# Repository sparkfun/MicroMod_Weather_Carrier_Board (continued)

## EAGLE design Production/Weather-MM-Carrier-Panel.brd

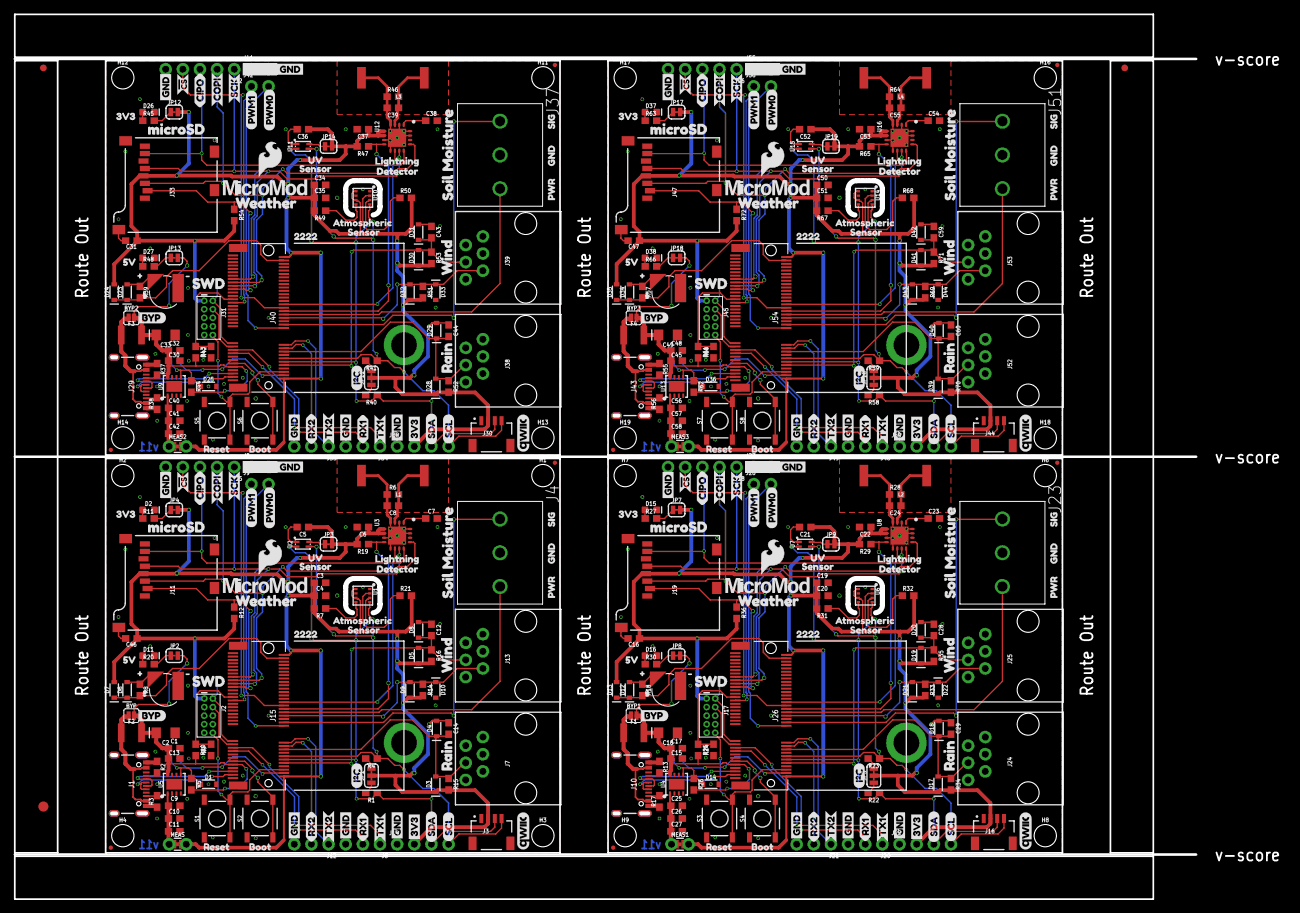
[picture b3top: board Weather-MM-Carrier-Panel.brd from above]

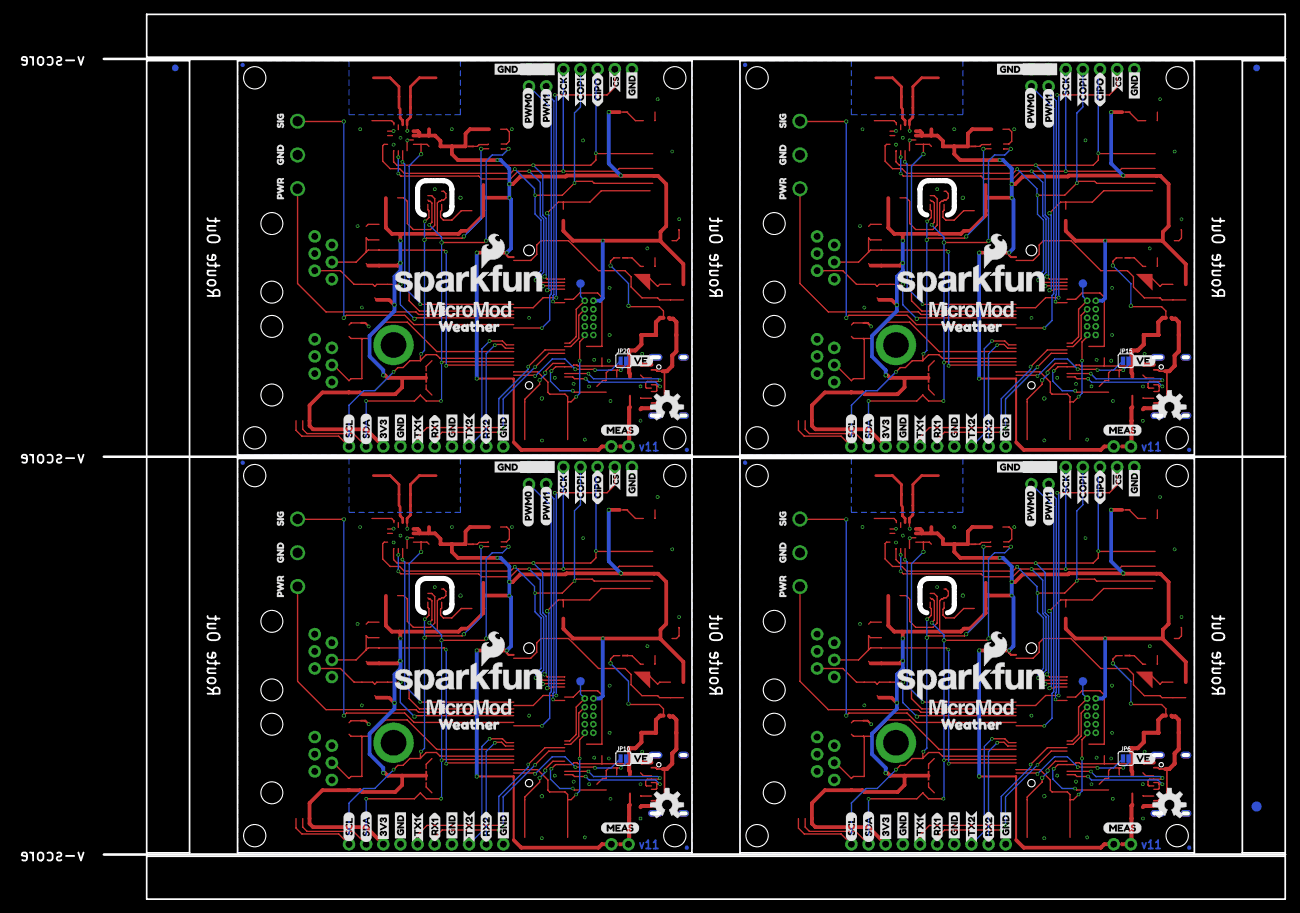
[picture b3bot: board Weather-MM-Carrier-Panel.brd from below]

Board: 2 copper layers, 175.0 x 131.1 mm, 630 parts (127 on the bottom side), 196 nets.

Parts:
BT1, BT2, BT3, BT4: ML414H; ML414H_IV01E
BYP, BYP1, BYP2, BYP3: JUMPER-SMT_2_NO_SILK; SMT-JUMPER_2_NO_SILK
C1, C3, C4, C5, C12, C14, C16, C17, C19, C20, C21, C28, C29, C31, C32, C34, C35, C36, C43, C44, C46, C47, C48, C50, C51, C52, C59, C60: 0.1uF; 0603
C2, C18, C33, C49: 10uF; EIA3216
C6, C10, C22, C26, C37, C41, C53, C57: 1.0uF; 0603
C7, C9, C23, C25, C38, C40, C54, C56: 10uF; 0603
C8, C24, C39, C55: 1nF; 0603
C11, C13, C15, C27, C30, C42, C45, C58: 0.22uF; 0603
D1, D14, D25, D36: 3.3V; SOD-323
D2, D11, D15, D16, D26, D27, D37, D38: RED; LED-0603
D3, D4, D5, D8, D9, D10, D17, D18, D19, D20, D21, D22, D28, D29, D30, D31, D32, D33, D39, D40, D41, D42, D43, D44: 250mA/100V; SOD-323
D6, D12, D23, D34: 3A/10V/280mV; SOD-323
D7, D13, D24, D35: 1A/23V/620mV; SOD-323
E$1, E$2, E$3, E$4: FIDUCIAL-1X2
E$5, E$6: FIDUCIAL-1.5X3
F1, F2, F3, F4: 6V/2A; 1210
FD1, FD2, FD3, FD4, FD5, FD6, FD7, FD8, FD9, FD10, FD11, FD12, FD13, FD14, FD15, FD16: FIDUCIALUFIDUCIAL; FIDUCIAL-MICRO
H1, H2, H3, H4, H6, H7, H8, H9, H11, H12, H13, H14, H16, H17, H18, H19: STAND-OFF
H5, H10, H15, H20: STAND-OFF-REFLOW2.5MM_TALL; STAND-OFF-REFLOW-M2.5
J1, J10, J29, J43: USB-C-16P-2LAYER-PADS
J2, J17, J31, J45: JTAG; 2X5-PTH-1.27MM
J3, J16, J30, J44: QWIIC_RIGHT_ANGLE; JST04_1MM_RA
J4, J23, J37, J51: LATCHTERMINAL-5MM-3
J5, J18, J32, J46: 1X05_NO_SILK
J6, J12, J20, J21, J34, J35, J48, J49: 1X03_NO_SILK
J7, J24, J38, J52: RJ11 - RAIN; RJ11-6
J8, J9, J27, J28, J41, J42, J55, J56: 1X02_NO_SILK
J11, J19, J33, J47: microSD; MICRO-SD-SOCKET
J13, J25, J39, J53: RJ11 - WIND; RJ11-6
J14, J22, J36, J50: 1X04_NO_SILK
J15, J26, J40, J54: MICROMOD-2222-C; M.2-CONNECTOR-E
JP1, JP5, JP11, JP16: SMT-JUMPER_3_2-NC_TRACE_SILK
JP2, JP8, JP13, JP18: VIN LED; SMT-JUMPER_2_NC_TRACE_SILK
JP3, JP9, JP14, JP19: UV; SMT-JUMPER_2_NC_TRACE_SILK
JP4, JP7, JP12, JP17: 3V3 LED; SMT-JUMPER_2_NC_TRACE_SILK
JP6, JP10, JP15, JP20: VE; SMT-JUMPER_2_NO_SILK
L1, L2, L3, L4: 100uH; MA5532-AE
LOGO1, LOGO6, LOGO9, LOGO12: SFE_LOGO_NAME_FLAME.2_INCH; SFE_LOGO_NAME_FLAME_.2
LOGO2, LOGO4, LOGO7, LOGO10: QWIIC_LOGO_CONNECTOR; QWIIC_5.5MM
LOGO3, LOGO5, LOGO8, LOGO11: OSHW-LOGOM; OSHW-LOGO-M
MEAS, MEAS1, MEAS2, MEAS3: COMBO-JUMPER_2_NC_TRACE
R1, R4, R22, R23, R40, R41, R58, R59: 2.2k; 0603
R2, R3, R13, R17, R37, R38, R55, R56: 5.1k; 0603
R5, R12, R19, R26, R29, R36, R44, R47, R54, R62, R65, R72: 100k; 0603
R6, R7, R9, R14, R21, R24, R28, R31, R32, R33, R42, R46, R49, R50, R51, R60, R64, R67, R68, R69: 10k; 0603
R8, R18, R39, R57: 3.3k; 0603
R10, R25, R43, R61: 20k; 0603
R11, R20, R27, R30, R45, R48, R63, R66: 1k; 0603
R15, R16, R34, R35, R52, R53, R70, R71: 43k; 0603
S1, S3, S5, S7: Reset; TACTILE_SWITCH_SMD_5.2MM
S2, S4, S6, S8: BOOT; TACTILE_SWITCH_SMD_5.2MM
TP1, TP2, TP3, TP4: TEST-POINT3X5; PAD.03X.05
U1, U6, U10, U14: BME280; LGA-8-2.5X2.5
U2, U7, U11, U15: VEML6075; VEML6075_A3OP
U3, U8, U12, U16: AS3935; 16LD_MLPQ
U4, U5, U9, U13: AP7361C-33FGEUDFN-8; UDFN-8
U$1, U$119, U$188, U$257: 3V31
U$2, U$26, U$139, U$208: RESET3
U$3, U$110, U$179, U$248: RAIN1
U$4, U$57, U$113, U$128, U$182, U$197, U$251, U$266: GND0
U$5, U$51, U$140, U$209: MEAS
U$6, U$11, U$23, U$32, U$33, U$36, U$42, U$45, U$53, U$54, U$74, U$75, U$79, U$80, U$82, U$86, U$89, U$90, U$96, U$99, U$143, U$144, U$148, U$149, U$151, U$155, U$158, U$159, U$165, U$168, U$212, U$213, U$217, U$218, U$220, U$224, U$227, U$228, U$234, U$237: GND_P
U$7, U$8, U$130, U$131, U$199, U$200, U$268, U$269: COPI0
U$9, U$49, U$72, U$94, U$141, U$163, U$210, U$232: SCK_O
U$10, U$52, U$73, U$95, U$142, U$164, U$211, U$233: !CS_O
U$12, U$24, U$114, U$127, U$183, U$196, U$252, U$265: PWR2
U$13, U$63, U$115, U$129, U$184, U$198, U$253, U$267: SIG1
U$14, U$135, U$204, U$273: BYP0
U$15, U$61, U$98, U$100, U$167, U$169, U$236, U$238: PWM10
U$16, U$58, U$116, U$122, U$185, U$191, U$254, U$260: WEATHER4
U$17, U$30, U$101, U$104, U$170, U$173, U$239, U$242: RX25
U$18, U$120, U$189, U$258: 5V0
U$19, U$76, U$145, U$214: BOOT2
U$20, U$123, U$192, U$261: ATMOSPHERIC0
U$21, U$138, U$207, U$276: VE0
U$22, U$107, U$176, U$245: LIGHTNING8
U$25, U$29, U$77, U$87, U$146, U$156, U$215, U$225: RX10
U$27, U$50, U$136, U$137, U$205, U$206, U$274, U$275: CIPO0
U$28, U$56, U$102, U$103, U$171, U$172, U$240, U$241: TX24
U$31, U$41, U$78, U$88, U$147, U$157, U$216, U$226: TX13
U$34, U$108, U$177, U$246: SENSOR7
U$35, U$117, U$186, U$255: MICROSD0
U$37, U$81, U$150, U$219: I2C
U$38, U$46, U$83, U$91, U$152, U$160, U$221, U$229: 3V3_P
U$39, U$47, U$84, U$92, U$153, U$161, U$222, U$230: SDA_IO
U$40, U$48, U$85, U$93, U$154, U$162, U$223, U$231: SCL_IO
U$43, U$118, U$187, U$256: SWD1
U$44, U$121, U$190, U$259: SFE_LOGO_FLAME_.2
U$55, U$97, U$166, U$235: 22229
U$59, U$60, U$105, U$106, U$174, U$175, U$243, U$244: PWM01
U$62, U$109, U$178, U$247: UV6
U$64, U$124, U$193, U$262: SENSOR1
U$65, U$111, U$180, U$249: SOIL_MOISTURE2
U$66, U$112, U$181, U$250: WIND0
U$67, U$68, U$125, U$126, U$194, U$195, U$263, U$264: MICROMOD_LOGO_.5
U$69, U$132, U$201, U$270: #0
U$70, U$133, U$202, U$271: #1
U$71, U$134, U$203, U$272: DETECTOR2

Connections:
3.3V: C3.1, C4.1, C5.1, C6.1, C46.1, D3.C, D5.C, D7.A, D9.C, J2.1, J3.2, J11.VCC, J14.2, J15.2, J15.74, JP1.2, JP3.2, JP4.2, MEAS.2, MEAS.4, R7.2, R12.2, R14.2, R15.2, R16.2, R19.2, R21.2, U1.6, U1.8, U3.5, U3.6
3.3V1: C16.1, C19.1, C20.1, C21.1, C22.1, D13.A, D17.C, D19.C, D21.C, J16.2, J17.1, J19.VCC, J22.2, J26.2, J26.74, JP5.2, JP7.2, JP9.2, MEAS1.2, MEAS1.4, R29.2, R31.2, R32.2, R33.2, R34.2, R35.2, R36.2, U6.6, U6.8, U8.5, U8.6
3.3V2: C31.1, C34.1, C35.1, C36.1, C37.1, D24.A, D28.C, D30.C, D32.C, J30.2, J31.1, J33.VCC, J36.2, J40.2, J40.74, JP11.2, JP12.2, JP14.2, MEAS2.2, MEAS2.4, R47.2, R49.2, R50.2, R51.2, R52.2, R53.2, R54.2, U10.6, U10.8, U12.5, U12.6
3.3V3: C47.1, C50.1, C51.1, C52.1, C53.1, D35.A, D39.C, D41.C, D43.C, J44.2, J45.1, J47.VCC, J50.2, J54.2, J54.74, JP16.2, JP17.2, JP19.2, MEAS3.2, MEAS3.4, R65.2, R67.2, R68.2, R69.2, R70.2, R71.2, R72.2, U14.6, U14.8, U16.5, U16.6
3.3V_EN: J15.4, JP6.1
3.3V_EN1: J26.4, JP10.1
3.3V_EN2: J40.4, JP15.1
3.3V_EN3: J54.4, JP20.1
!BOOT!: J15.11, S2.3, S2.4
!BOOT!1: J26.11, S4.3, S4.4
!BOOT!2: J40.11, S6.3, S6.4
!BOOT!3: J54.11, S8.3, S8.4
!RESET!: J2.10, J15.6, S1.3, S1.4
!RESET!1: J17.10, J26.6, S3.3, S3.4
!RESET!2: J31.10, J40.6, S5.3, S5.4
!RESET!3: J45.10, J54.6, S7.3, S7.4
GND: BT1.-, C1.2, C2.-, C3.2, C4.2, C5.2, C6.2, C7.2, C8.2, C9.2, C10.2, C11.2, C12.1, C13.2, C14.1, C46.2, D1.A, D2.C, D4.A, D8.A, D10.A, D11.C, H5.1, J1.GND, J1.GND2, J2.3, J2.5, J2.9, J3.1, J4.2, J5.5, J6.3, J7.4, J8.1, J8.2, J11.CD1, J11.GND, J11.GND1, J11.GND3, J12.3, J13.4, J13.5, J14.1, J15.1, J15.7, J15.33, J15.36, J15.39, J15.45, J15.75, L1.2, R2.1, R3.1, R6.1, R9.1, S1.1, S1.2, S2.1, S2.2, U1.1, U1.7, U2.1, U3.2, U3.4, U3.7, U3.9, U3.15, U3.16, U3.17, U5.4, U5.EP
GND1: BT2.-, C15.2, C16.2, C17.2, C18.-, C19.2, C20.2, C21.2, C22.2, C23.2, C24.2, C25.2, C26.2, C27.2, C28.1, C29.1, D14.A, D15.C, D16.C, D18.A, D20.A, D22.A, H10.1, J10.GND, J10.GND2, J16.1, J17.3, J17.5, J17.9, J18.5, J19.CD1, J19.GND, J19.GND1, J19.GND3, J20.3, J21.3, J22.1, J23.2, J24.4, J25.4, J25.5, J26.1, J26.7, J26.33, J26.36, J26.39, J26.45, J26.75, J27.1, J27.2, L2.2, R13.1, R17.1, R24.1, R28.1, S3.1, S3.2, S4.1, S4.2, U4.4, U4.EP, U6.1, U6.7, U7.1, U8.2, U8.4, U8.7, U8.9, U8.15, U8.16, U8.17
GND2: BT3.-, C30.2, C31.2, C32.2, C33.-, C34.2, C35.2, C36.2, C37.2, C38.2, C39.2, C40.2, C41.2, C42.2, C43.1, C44.1, D25.A, D26.C, D27.C, D29.A, D31.A, D33.A, H15.1, J29.GND, J29.GND2, J30.1, J31.3, J31.5, J31.9, J32.5, J33.CD1, J33.GND, J33.GND1, J33.GND3, J34.3, J35.3, J36.1, J37.2, J38.4, J39.4, J39.5, J40.1, J40.7, J40.33, J40.36, J40.39, J40.45, J40.75, J41.1, J41.2, L3.2, R37.1, R38.1, R42.1, R46.1, S5.1, S5.2, S6.1, S6.2, U9.4, U9.EP, U10.1, U10.7, U11.1, U12.2, U12.4, U12.7, U12.9, U12.15, U12.16, U12.17
GND3: BT4.-, C45.2, C47.2, C48.2, C49.-, C50.2, C51.2, C52.2, C53.2, C54.2, C55.2, C56.2, C57.2, C58.2, C59.1, C60.1, D36.A, D37.C, D38.C, D40.A, D42.A, D44.A, H20.1, J43.GND, J43.GND2, J44.1, J45.3, J45.5, J45.9, J46.5, J47.CD1, J47.GND, J47.GND1, J47.GND3, J48.3, J49.3, J50.1, J51.2, J52.4, J53.4, J53.5, J54.1, J54.7, J54.33, J54.36, J54.39, J54.45, J54.75, J55.1, J55.2, L4.2, R55.1, R56.1, R60.1, R64.1, S7.1, S7.2, S8.1, S8.2, U13.4, U13.EP, U14.1, U14.7, U15.1, U16.2, U16.4, U16.7, U16.9, U16.15, U16.16, U16.17
HEADER_!CS!: J5.4, J15.44
HEADER_!CS!1: J18.4, J26.44
HEADER_!CS!2: J32.4, J40.44
HEADER_!CS!3: J46.4, J54.44
I2C_SCL: J3.4, J14.4, J15.14, R4.1, U1.4, U2.3
I2C_SCL1: J16.4, J22.4, J26.14, R23.1, U6.4, U7.3
I2C_SCL2: J30.4, J36.4, J40.14, R41.1, U10.4, U11.3
I2C_SCL3: J44.4, J50.4, J54.14, R59.1, U14.4, U15.3
I2C_SDA: J3.3, J14.3, J15.12, R1.1, U1.3, U2.2
I2C_SDA1: J16.3, J22.3, J26.12, R22.1, U6.3, U7.2
I2C_SDA2: J30.3, J36.3, J40.12, R40.1, U10.3, U11.2
I2C_SDA3: J44.3, J50.3, J54.12, R58.1, U14.3, U15.2
INP: C8.1, L1.1, R6.2, U3.3
INP1: C24.1, L2.1, R28.2, U8.3
INP2: C39.1, L3.1, R46.2, U12.3
INP3: C55.1, L4.1, R64.2, U16.3
LIGHTNING_!CS!: J15.42, R19.1, U3.8
LIGHTNING_!CS!1: J26.42, R29.1, U8.8
LIGHTNING_!CS!2: J40.42, R47.1, U12.8
LIGHTNING_!CS!3: J54.42, R65.1, U16.8
LIGHTNING_INT: J15.46, U3.10
LIGHTNING_INT1: J26.46, U8.10
LIGHTNING_INT2: J40.46, U12.10
LIGHTNING_INT3: J54.46, U16.10
unnamed: C9.1, C10.1, C11.1, MEAS.1, MEAS.3, U5.1
unnamed: JP1.3, R4.2
unnamed: JP1.1, R1.2
unnamed: JP4.1, R11.2
unnamed: JP2.1, R20.2
unnamed: D2.A, R11.1
unnamed: JP3.1, U2.4
unnamed: R7.1, U1.5
unnamed: J10.A5, R13.2
unnamed: J1.A5, R2.2
unnamed: J1.B5, R3.2
unnamed: J10.B5, R17.2
unnamed: BT2.+, D12.A, R18.1
unnamed: BT1.+, D6.A, R8.1
unnamed: C7.1, U3.1
unnamed: D11.A, R20.1
unnamed: JP5.3, R23.2
unnamed: JP5.1, R22.2
unnamed: R21.1, U1.2
unnamed: C25.1, C26.1, C27.1, MEAS1.1, MEAS1.3, U4.1
unnamed: JP7.1, R27.2
unnamed: D15.A, R27.1
unnamed: C23.1, U8.1
unnamed: JP8.1, R30.2
unnamed: D16.A, R30.1
unnamed: R32.1, U6.2
unnamed: R31.1, U6.5
unnamed: JP9.1, U7.4
unnamed: J29.A5, R37.2
unnamed: J29.B5, R38.2
unnamed: BT3.+, D23.A, R39.1
unnamed: JP11.3, R41.2
unnamed: JP11.1, R40.2
unnamed: C40.1, C41.1, C42.1, MEAS2.1, MEAS2.3, U9.1
unnamed: JP12.1, R45.2
unnamed: D26.A, R45.1
unnamed: C38.1, U12.1
unnamed: JP13.1, R48.2
unnamed: D27.A, R48.1
unnamed: R50.1, U10.2
unnamed: R49.1, U10.5
unnamed: JP14.1, U11.4
unnamed: J43.A5, R55.2
unnamed: J43.B5, R56.2
unnamed: BT4.+, D34.A, R57.1
unnamed: JP16.3, R59.2
unnamed: JP16.1, R58.2
unnamed: C56.1, C57.1, C58.1, MEAS3.1, MEAS3.3, U13.1
unnamed: JP17.1, R63.2
unnamed: D37.A, R63.1
unnamed: C54.1, U16.1
unnamed: JP18.1, R66.2
unnamed: D38.A, R66.1
unnamed: R68.1, U14.2
unnamed: R67.1, U14.5
unnamed: JP19.1, U15.4
PWM0: J9.2, J15.32
PWM1: J9.1, J15.47
PWM2: J26.32, J28.2
PWM3: J26.47, J28.1
PWM4: J40.32, J42.2
PWM5: J40.47, J42.1
PWM6: J54.32, J56.2
PWM7: J54.47, J56.1
RAIN: C14.2, D3.A, D4.C, J7.3, J15.18, R15.1
RAIN1: C29.2, D17.A, D18.C, J24.3, J26.18, R34.1
RAIN2: C44.2, D28.A, D29.C, J38.3, J40.18, R52.1
RAIN3: C60.2, D39.A, D40.C, J52.3, J54.18, R70.1
RTC_3V: D6.C, D7.C, J15.72, R8.2
RTC_3V1: D12.C, D13.C, J26.72, R18.2
RTC_3V2: D23.C, D24.C, J40.72, R39.2
RTC_3V3: D34.C, D35.C, J54.72, R57.2
RX1: J6.2, J15.19
RX2: J12.2, J15.20
RX3: J20.2, J26.19
RX4: J21.2, J26.20
RX5: J34.2, J40.19
RX6: J35.2, J40.20
RX7: J48.2, J54.19
RX8: J49.2, J54.20
SD_!CS!: J11.CS/DAT3, J15.55, R12.1
SD_!CS!1: J19.CS/DAT3, J26.55, R36.1
SD_!CS!2: J33.CS/DAT3, J40.55, R54.1
SD_!CS!3: J47.CS/DAT3, J54.55, R72.1
SOIL_MOIST_PWR: J4.3, J15.40
SOIL_MOIST_PWR1: J23.3, J26.40
SOIL_MOIST_PWR2: J37.3, J40.40
SOIL_MOIST_PWR3: J51.3, J54.40
SOIL_MOIST_SIG: J4.1, J15.34
SOIL_MOIST_SIG1: J23.1, J26.34
SOIL_MOIST_SIG2: J37.1, J40.34
SOIL_MOIST_SIG3: J51.1, J54.34
SPI_CIPO: J5.3, J11.DO/DAT0, J15.61, U3.12
SPI_CIPO1: J18.3, J19.DO/DAT0, J26.61, U8.12
SPI_CIPO2: J32.3, J33.DO/DAT0, J40.61, U12.12
SPI_CIPO3: J46.3, J47.DO/DAT0, J54.61, U16.12
SPI_COPI: J5.2, J11.DI/CMD, J15.59, U3.13
SPI_COPI1: J18.2, J19.DI/CMD, J26.59, U8.13
SPI_COPI2: J32.2, J33.DI/CMD, J40.59, U12.13
SPI_COPI3: J46.2, J47.DI/CMD, J54.59, U16.13
SPI_SCK: J5.1, J11.SCLK, J15.57, U3.11
SPI_SCK1: J18.1, J19.SCLK, J26.57, U8.11
SPI_SCK2: J32.1, J33.SCLK, J40.57, U12.11
SPI_SCK3: J46.1, J47.SCLK, J54.57, U16.11
SWDCK: J2.4, J15.21
SWDCK1: J17.4, J26.21
SWDCK2: J31.4, J40.21
SWDCK3: J45.4, J54.21
SWDIO: J2.2, J15.23, TP1.P$1
SWDIO1: J17.2, J26.23, TP2.P$1
SWDIO2: J31.2, J40.23, TP3.P$1
SWDIO3: J45.2, J54.23, TP4.P$1
TX1: J6.1, J15.17
TX2: J12.1, J15.22
TX3: J20.1, J26.17
TX4: J21.1, J26.22
TX5: J34.1, J40.17
TX6: J35.1, J40.22
TX7: J48.1, J54.17
TX8: J49.1, J54.22
USB_D+: J1.A6, J1.B6, J15.3
USB_D+1: J10.A6, J10.B6, J26.3
USB_D+2: J29.A6, J29.B6, J40.3
USB_D+3: J43.A6, J43.B6, J54.3
USB_D-: J1.A7, J1.B7, J15.5
USB_D-1: J10.A7, J10.B7, J26.5
USB_D-2: J29.A7, J29.B7, J40.5
USB_D-3: J43.A7, J43.B7, J54.5
VIN: BYP.2, C1.1, C2.+, C13.1, F2.2, J15.9, JP2.2, R5.2, R10.2, U5.8
VIN1: BYP1.2, C15.1, C17.1, C18.+, F1.2, J26.9, JP8.2, R25.2, R26.2, U4.8
VIN2: BYP2.2, C30.1, C32.1, C33.+, F3.2, J40.9, JP13.2, R43.2, R44.2, U9.8
VIN3: BYP3.2, C45.1, C48.1, C49.+, F4.2, J54.9, JP18.2, R61.2, R62.2, U13.8
VIN/1: J26.49, R24.2, R25.1
VIN/2: J40.49, R42.2, R43.1
VIN/3: J15.49, R9.2, R10.1
VIN/4: J54.49, R60.2, R61.1
VREG_EN: D1.C, JP6.2, R5.1, U5.5
VREG_EN1: D14.C, JP10.2, R26.1, U4.5
VREG_EN2: D25.C, JP15.2, R44.1, U9.5
VREG_EN3: D36.C, JP20.2, R62.1, U13.5
V_USB: BYP.1, F2.1, J1.VBUS1, J1.VBUS2
V_USB1: BYP1.1, F1.1, J10.VBUS1, J10.VBUS2
V_USB2: BYP2.1, F3.1, J29.VBUS1, J29.VBUS2
V_USB3: BYP3.1, F4.1, J43.VBUS1, J43.VBUS2
WDIR: D9.A, D10.C, J13.2, J15.38, R14.1
WDIR1: D21.A, D22.C, J25.2, J26.38, R33.1
WDIR2: D32.A, D33.C, J39.2, J40.38, R51.1
WDIR3: D43.A, D44.C, J53.2, J54.38, R69.1
WSPEED: C12.2, D5.A, D8.C, J13.3, J15.10, R16.1
WSPEED1: C28.2, D19.A, D20.C, J25.3, J26.10, R35.1
WSPEED2: C43.2, D30.A, D31.C, J39.3, J40.10, R53.1
WSPEED3: C59.2, D41.A, D42.C, J53.3, J54.10, R71.1

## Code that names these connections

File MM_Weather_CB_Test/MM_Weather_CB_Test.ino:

/*
  MicroMod Weather Carrier Board Test

  To Be Tested:
  DONE: Stat led
  DONE: BME280 - temp, pressure, humidity (I2C)
  DONE: VEML6075 - UV sensor (I2C)
  AS3935 - lightning detector (SPI)
  DONE: Soil moisture connector
  DONE: Wind Meter
  DONE: Rain Meter
  DONE: uSD card
  Other
    PWM0/1 -- 1 doesn't work
    DONE: Qwiic Connector
    TX/RX 1/2 -- tested in separate sketch, need diff PB to test TX/RX2
    VIN/3 -- doesn't work
*/

#include <Wire.h>
#include <SPI.h>
#include <SD.h>
#include "SparkFunBME280.h"
#include <SparkFun_VEML6075_Arduino_Library.h>
#include <SparkFun_Alphanumeric_Display.h>  

BME280 tempSensor;
VEML6075 uv;
Sd2Card card;
SdVolume volume;
HT16K33 display;  //For testing the qwiic connector

int STAT_LED = 19;
int moist_val = 0;  //Variable for storing moisture value
int soilPin = A32;  //Pin number that measures analog moisture signal
int soilPower = A16;  //Pin number that will power the soil moisture sensor

int WSPEED = 1; //Digital I/O pin for wind speed
int WDIR = A35; //Analog pin for wind direction
int RAIN = 2;   //Digital I/O pin for rain fall
volatile bool rain_flag = false;
volatile bool wind_flag = false;

const int SD_chipSelect = 23;
//const int SD_chipSelect = CS; //Chip select pin for SD card
const int PIN_PWM0 = 44;
const int PIN_PWM1 = 45;


//TODO: change IRQ's to return flags, variables need to be declared volatile
//Function is called every time the rain bucket tips
void rainIRQ()
{
  rain_flag = true;
}

//Function is called when the magnet in the anemometer is activated
void wspeedIRQ()
{
  wind_flag = true;
}

void setup() {
  Serial.begin(115200);
  Serial.println("MicroMod Weather Carrier Board Test");
  Serial.println();

  Wire.begin();

  if (tempSensor.beginI2C() == false) { //Begin communication over I2C
    Serial.println("BME280 did not respond.");
    while(1); //Freeze
  }
  if (uv.begin() == false) {
    Serial.println("VEML6075 did not respond.");
    while(1);
  }
  
  pinMode(STAT_LED, OUTPUT);
  pinMode(soilPower, OUTPUT);
  digitalWrite(soilPower, LOW);

  //Initialization for weather meter
  pinMode(WSPEED, INPUT_PULLUP);  //Input from wind meters windspeed sensor
  pinMode(RAIN, INPUT_PULLUP);    //Input from wind meters rain gauge sensor
  //attach external interrupt pins to IRQ functions
  attachInterrupt(digitalPinToInterrupt(RAIN), rainIRQ, FALLING);
  attachInterrupt(digitalPinToInterrupt(WSPEED), wspeedIRQ, FALLING);
  //turn on interrupts
  interrupts();

  testSD();
  testRemainingPeripherals();
}

// the loop function runs over and over again forever
void loop() {
  Serial.println();
  Serial.println("BME280 Check");
  Serial.print("Temperature: ");
  Serial.println(tempSensor.readTempF(), 2);
  Serial.print("Humidity: ");
  Serial.println(tempSensor.readFloatHumidity(), 0);
  Serial.print("Pressure: ");
  Serial.println(tempSensor.readFloatPressure(), 0);
  Serial.print("Altitude: ");
  Serial.println(tempSensor.readFloatAltitudeFeet(), 1);
  Serial.println();

  Serial.println("VEML6075 Check");
  Serial.println(String(uv.uva()) + ", " + String(uv.uvb()) + ", "+ String(uv.index()));
  Serial.println();

  Serial.println("Soil Moisture Sensor Check");
  Serial.print("Soil Moisture = ");
  Serial.println(readSoil());

  Serial.println("Weather Meter Wind Direction Check");
  Serial.print("Wind direction: ");
  Serial.print(get_wind_direction());
  Serial.println(" degrees");
  //Check interrupt flags
  if (rain_flag == true){
    Serial.println("RRRRRAAAAIIIINNN!!!");
    rain_flag = false;
  }
  if (wind_flag == true){
    Serial.println("Wind click!");
    wind_flag = false;
  }
  
  digitalWrite(STAT_LED, HIGH);   // turn the LED on (HIGH is the voltage level)
  delay(1000);                       // wait for a second
  digitalWrite(STAT_LED, LOW);    // turn the LED off by making the voltage LOW
  delay(1000);                       // wait for a second

  delay(2000);
}

void testSD() {
  //SD Card test
  Serial.println("Initializing SD card...");
  
  if (!card.init(SPI_HALF_SPEED, SD_chipSelect)) {
    Serial.println("initialization failed. Things to check:");
    Serial.println("* is a card inserted?");
    Serial.println("* is your wiring correc?");
    Serial.println("* did you change the chipSelect pin to match your module?");
    while(1);
  } else {
    Serial.println("Wiring is correct and a card is present.");
  }

  //print the type of card
  Serial.println();
  Serial.print("Card type:          ");
  switch (card.type()) {
    case SD_CARD_TYPE_SD1:
      Serial.println("SD1");
      break;
    case SD_CARD_TYPE_SD2:
      Serial.println("SD2");
      break;
    case SD_CARD_TYPE_SDHC:
      Serial.println("SDHC");
      break;
    default:
      Serial.println("Unknown");
  }

  if (!volume.init(card)) {
    Serial.println("Could not find FAT16/FAT32 partition. \nMake sure you've formatted the card");
    while(1);
  }
  
  //print the type and size of hte first FAT-type volume
  uint32_t volumesize;
  Serial.print("Volume type is:     FAT");
  Serial.println(volume.fatType(), DEC);

  volumesize = volume.blocksPerCluster();
  volumesize *= volume.clusterCount();
  volumesize /= 2;
  volumesize /= 1024;
  Serial.print("Volume size (Gb): ");
  Serial.println((float)volumesize / 1024.0);
}

int readSoil() {
  //Power Senor
  digitalWrite(soilPower, HIGH);
  delay(10);
  moist_val = analogRead(soilPin);  //Read the SIG value from sensor
  digitalWrite(soilPower, LOW); //Turn the sensor off
  return moist_val; //Return current moisture value
}

int get_wind_direction()
{
  unsigned int adc;
  adc = analogRead(WDIR); //get the current readings from the sensor

  if (adc < 380) return (113);
  if (adc < 393) return (68);
  if (adc < 414) return (90);
  if (adc < 456) return (158);
  if (adc < 508) return (135);
  if (adc < 551) return (203);
  if (adc < 615) return (180);
  if (adc < 680) return (23);
  if (adc < 746) return (45);
  if (adc < 801) return (248);
  if (adc < 833) return (225);
  if (adc < 878) return (338);
  if (adc < 913) return (0);
  if (adc < 940) return (293);
  if (adc < 967) return (315);
  if (adc < 990) return (270);
  return (-1);
}

void testRemainingPeripherals() {
  Serial.println();
  //Test Qwiic Connector
  Serial.println("Test Qwiic Connector");
  if (display.begin() == false)
  {
    Serial.println("Alphanumeric did not acknowledge! Freezing.");
    while(1);
  }
  Serial.println("Alphanumeric acknowledged.");
  display.print("Milk");
  Serial.println();
  
  //Test PWM0/1
  Serial.println("Test PWM0/1. Use multimeter to verify.");
  analogWrite(PIN_PWM0, 125);
//  analogWrite(PIN_PWM1, 125); //TODO: this one doesn't work
  Serial.println();

  //Test VIN/3
  Serial.println("VIN/3 Test");
  analogReadResolution(14);
  int temp = analogRead(31);
//  temp = (temp * 3 * 2)/16384;
  Serial.println(temp);
}

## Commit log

2020-04-20 Initial commit
    Copy of machine learning carrier board eagle files
2020-04-20 Took out unnecessary blocks
    From copy of machine learning carrier board
2020-04-20 Added BME280 block
2020-04-20 Added UV (VEML6075) sensor block
2020-04-20 Added connector for soil moisture sensor
2020-04-22 Added RJ11 connectors for weather station add-on
2020-04-22 Added lightning detector block
2020-04-22 Fix net names
    Also renamed the sch/brd files to the right name
2020-04-27 Final schematic changes from review and Nate's notes
2020-04-29 Preliminary board layout
2020-04-29 Moved power LEDs
2020-04-29 Revised hardware layout
2020-04-29 Updated labels, condensed layout
2020-05-04 Routing
2020-05-04 Change MM pinout to new SPI standard
2020-05-05 Working on routing
2020-05-06 Routing finished for now
2020-05-06 Added silkscreen
2020-05-08 Removed ground plane from underneath lightning sensor coil
2020-05-12 Review changes
2020-05-12 Board review changes
2020-05-14 Review notes
2020-05-14 Revision changes
2020-05-15 Production files
2020-05-29 Added PROD_ID for latching terminal
2020-05-29 Remove Eagle backup files
2020-06-01 Implementing some changes from design check list
2020-06-09 Create MM_Weather_CB_Test.ino
    To test proto board
2020-06-25 Added jumper on 3.3V_EN
2020-07-01 Update weather meter IRQ's
2020-07-02 Update weather meter circuitry
2020-07-06 Changes from Nate
    Rotate soil moisture connector pins
    MOSI/MISO --> COPI, POCI
    Rotate LEDs
    +/- silk on batt
    Changed labels on jumpers
2020-07-06 Breaking big test script into small examples
2020-07-06 Creating example sketches
    Still need to test weather meter sketch with HW
2020-07-06 Fix typos
2020-07-07 Added serial test. Updated brd to pass design rules
2020-07-08 Changed "POCI" label to "CIPO"
2020-07-08 Impelemented design review changes
2020-07-13 Removed VIN/3 jumper
2020-07-14 Moved silkscreen
2020-07-14 QC Double check changes
    Added SWDIO test point, notes on VE jumper, measurements for standoffs, double check sparkle BOM, and DRC
2020-07-14 Changed VE jumper silk
2020-07-14 Add RTC/Batt example
2020-07-14 Fixed wire stubs?
2020-07-15 Added pullup resistor on CS line for SD card
2020-07-16 Update WeatherStation-MM-Carrier.brd
    Approved errors on DRC
2020-07-16 Moved 3.3V LED circuit to match 5V. Re-panelized and re-cammed
2020-08-05 Added interoperability for ESP32
2020-08-06 Update examples for interoperability
2020-08-10 Added interoperability for SAMD51
2020-08-10 Add functionality for interoperability
2020-08-11 Changed lightning CS from 10k to 100k (for ESP bootloading)
2020-08-11 Test sketches
2020-08-13 Deleting duplicate examples that are covered in test sketches
2020-08-17 Fixing MM artemis pins
2020-08-18 Update lightning example to have higher sensitivity
2020-08-20 Updating examples from Nate's notes
2020-08-25 Updated M.2 connector with increased tCream layer. Regenerated production files
2020-08-25 Renamed eagle project
    FromWeatherStation-MM-Carrier to Weather-MM-Carrier
2020-08-27 Adding README.md
    Initial commit of README file.
2020-08-27 Move "Production" folder
2020-09-10 Implemented SPI bus changes
    Re-panelized and new gerbers
2020-09-14 Tested the alternate weather meter example
2020-10-12 Update lilghtning detector examples
2020-12-03 Update names
    Updating Hardware board file names to match MicroMod naming conventions. Removing unneeded ZIP folder for Hardware files.
2021-01-13 Add Sd and lightning detector example
2023-07-05 Remove beerware/lemonadeware
    Remove mentions of beerware/lemonadeware
2023-07-05 Correct/Add code information
2023-07-05 Add license
2023-07-05 Delete MM-Weather-Carrier.zip
    Unnecessary zip file; files are already in the Hardware folder
2023-08-21 Update library and pins
    Update to use new Weather Meter Kit Arduino library
    Added pin declarations for other processor boards
